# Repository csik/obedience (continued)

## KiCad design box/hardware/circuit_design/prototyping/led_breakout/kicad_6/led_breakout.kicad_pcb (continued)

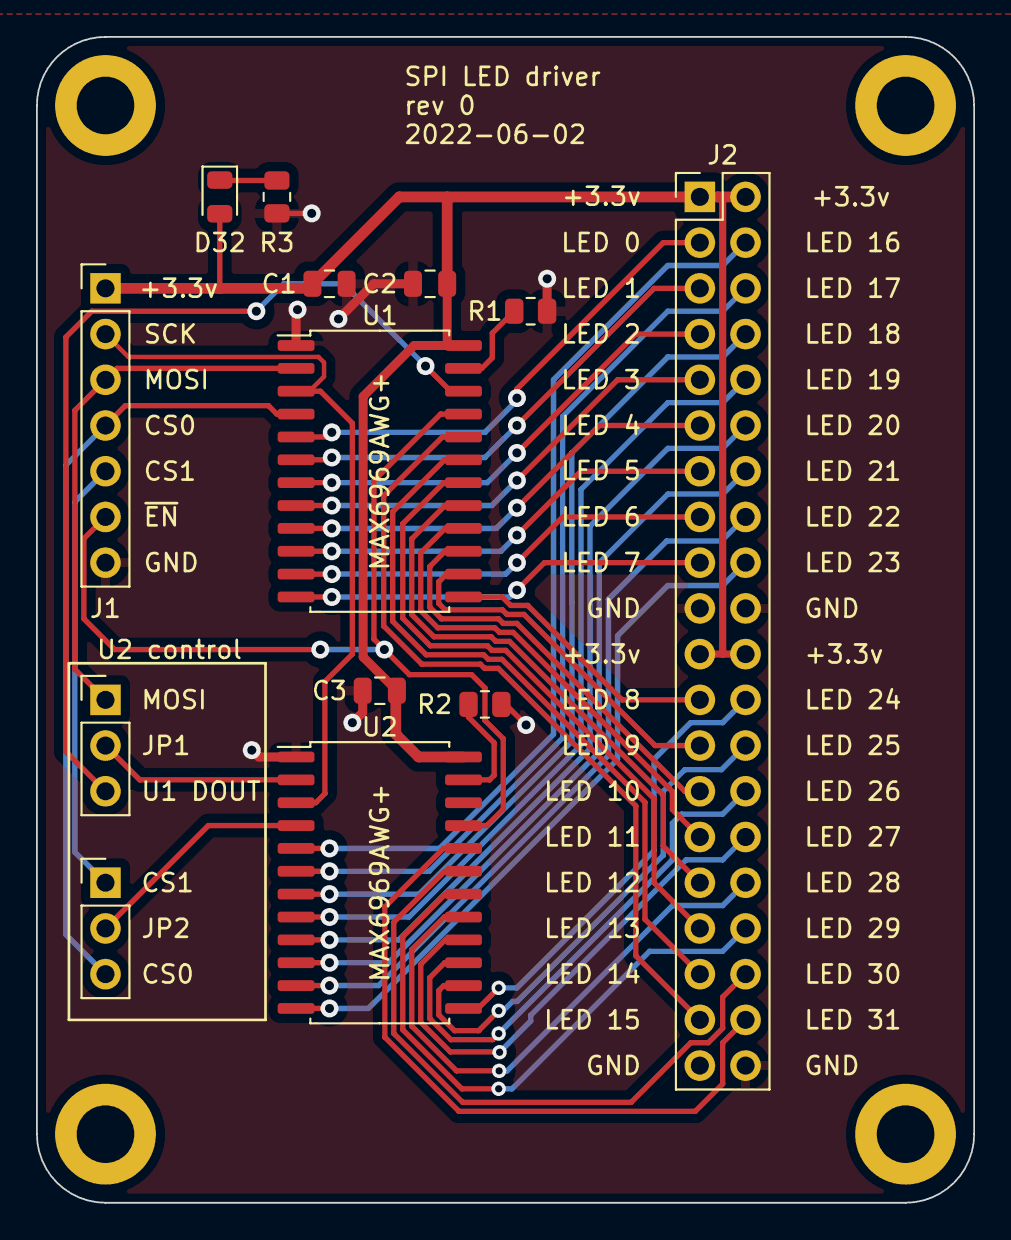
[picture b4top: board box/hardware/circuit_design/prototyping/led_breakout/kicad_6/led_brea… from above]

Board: 2 copper layers, 52.1 x 64.8 mm, 13 parts (0 on the bottom side), 45 nets.

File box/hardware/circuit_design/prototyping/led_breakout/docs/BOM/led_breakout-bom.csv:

Row,Description,Part,References,Value,Footprint,Quantity Per PCB,Status,Datasheet
1,Unpolarized capacitor,C,C2 C3,100n,C_0805_2012Metric,2, ,~
2,Unpolarized capacitor,C,C1,10u,C_0805_2012Metric,1, ,~
3,Light emitting diode,LED,D32,LED,LED_0805_2012Metric,1, ,~
4,"Generic connector, double row, 02x20, odd/even pin numbering scheme (row 1 odd numbers, row 2 even numbers), script generated (kicad-library-utils/schlib/autogen/connector/)",Conn_02x20_Odd_Even,J2,LED_header,PinHeader_2x20_P2.54mm_Vertical,1, ,~
5,"Generic connector, single row, 01x07, script generated (kicad-library-utils/schlib/autogen/connector/)",Conn_01x07,J1,rpi_port,PinHeader_1x07_P2.54mm_Vertical,1, ,~
6,"Jumper, 3-pole, pins 1+2 closed/bridged",Jumper_3_Bridged12,JP2,U2_CS_select,PinHeader_1x03_P2.54mm_Vertical,1, ,~
7,"Jumper, 3-pole, pins 1+2 closed/bridged",Jumper_3_Bridged12,JP1,U2_data_select,PinHeader_1x03_P2.54mm_Vertical,1, ,~
8,Resistor,R,R3,10k,R_0805_2012Metric,1, ,~
9,Resistor,R,R1 R2,R_led,R_0805_2012Metric,2, ,~
10,,MAX6969,U1 U2,MAX6969AWG+,SOIC-24W_7.5x15.4mm_P1.27mm,2, ,





Project info:
Schematic:,led_breakout
Variant:,default
Revision:,0
Date:,2022-06-02
KiCad Version:,6.0.6-3a73a75311~116~ubuntu22.04.1
Statistics:
Component Groups:,10
Component Count:,13 (9 SMD/ 4 THT)
Fitted Components:,13 (9 SMD/ 4 THT)
Number of PCBs:,1
Total Components:,13

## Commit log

2021-01-02 first obedience commmit, keeping webrtc example as submodule
2021-01-02 adding box code
2022-01-22 update box repo structure, add readmes
2022-01-22 add gitignore for KiCad files
2022-01-22 add prototyping breakout boards
2022-01-22 fix links to images
2022-02-10 make breakout boards both same size
2022-02-21 begin CADQuery front panel code
2022-02-21 update local readme
2022-03-03 Add triangular mounting hole components
2022-03-05 Add test code for SPI driven LEDs
2022-03-13 Add test code for SPI driven switches
2022-04-04 Add panel features, time operations
2022-04-04 Add panel output files
2022-04-05 Add write_single function, improve documentation
2022-04-05 Add analog voltmeter test code
2022-04-05 Update switches to use I2C instead of SPI
2022-04-07 Make I2C address jumpers MSB first
2022-04-24 Add I2C switch test script
2022-04-24 Fix some outdated comments
2022-06-02 Change LED and switch breakouts, use headers instead of components
2022-06-20 Update I2C test script
2022-06-20 Check boxes after I2C switch board test build
2022-06-20 Check boxes after LED board test build
2022-06-24 Use super-cool KiBot documentation generator for prototype PCBs
2022-06-24 Add .vscode dir to gitignore
2022-06-24 Update CADQuery code, remove lettering
2022-06-27 Remove old print statement
2022-07-21 Remove lines, fix vernier mounting holes, add holes around perimeter
2022-08-01 Embiggen holes for two aux lamps
2023-02-27 Add switch reader circuit board
2023-02-28 Add LED driver circuit board
2023-02-28 Add circuit board level READMEs, update main circuit design README
